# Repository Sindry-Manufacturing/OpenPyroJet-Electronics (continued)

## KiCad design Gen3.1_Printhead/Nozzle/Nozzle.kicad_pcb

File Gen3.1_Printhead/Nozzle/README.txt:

This directory contains KiCAD 5.1.x design files for a set of PCB's that make up the OpenPyroJet Gen 3.1 printhead. 
 
The directory could be better named as Printhead (as opposed to Nozzle), but I believe thats hard to do once a KiCAD project has been started?

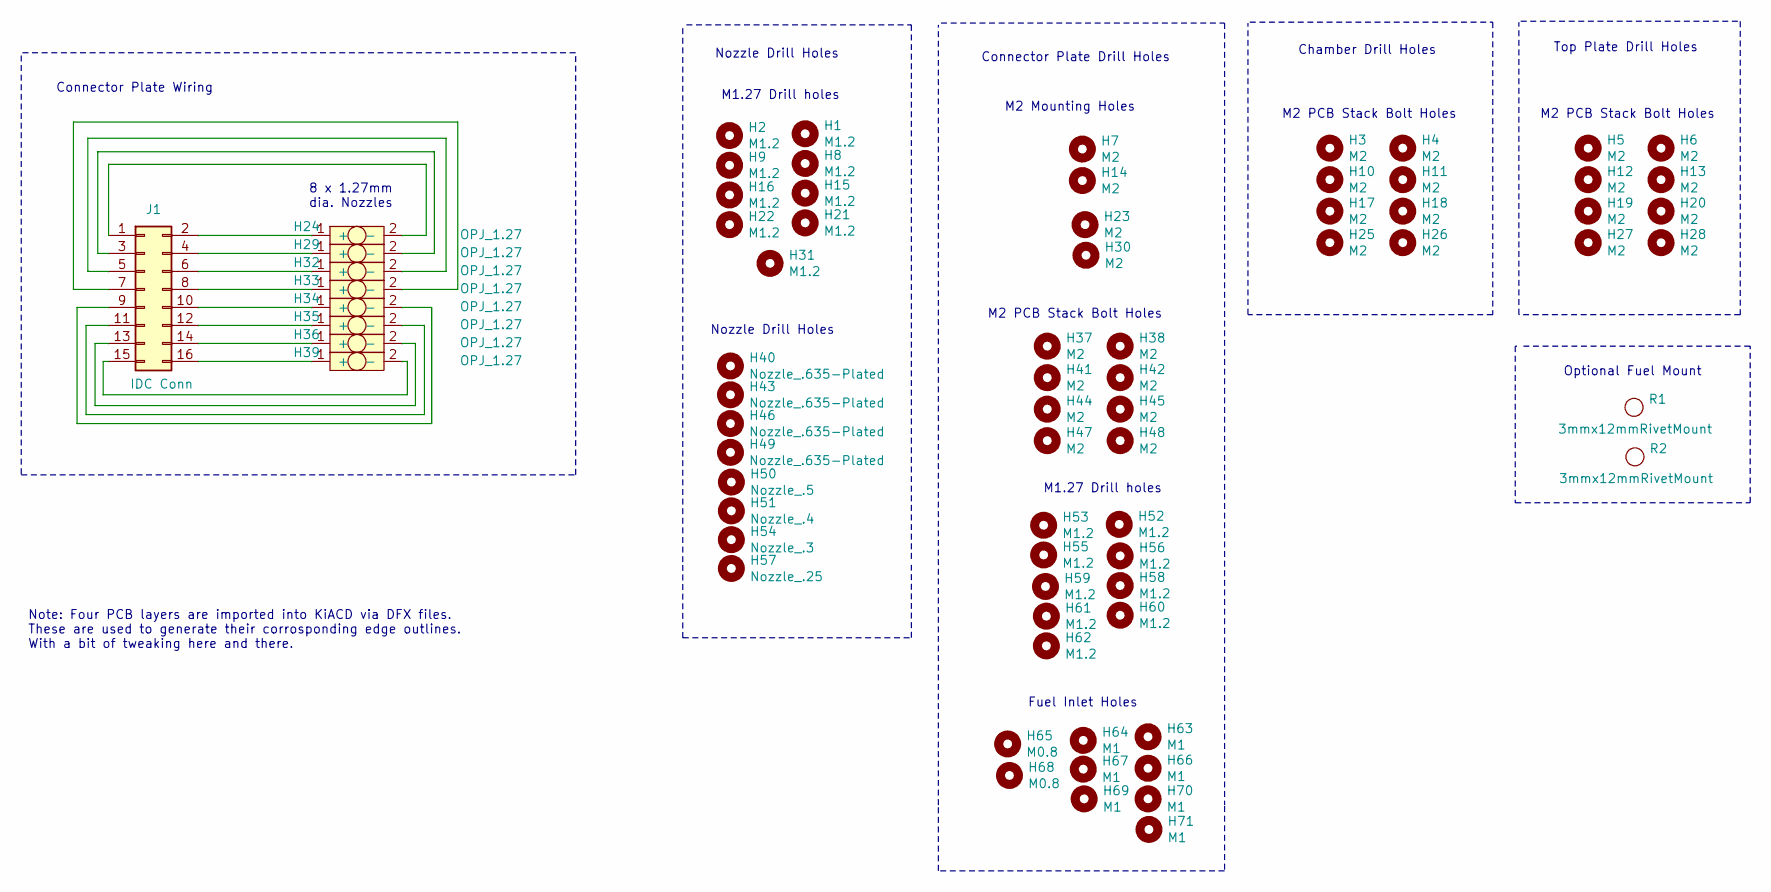
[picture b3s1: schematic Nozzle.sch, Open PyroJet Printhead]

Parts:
H1, H2, H8, H9, H15, H16, H21, H22, H31, H52, H53, H55, H56, H58, H59, H60, H61, H62: M1.2; MountingHole_1.2mm
H3, H4, H5, H6, H7, H10, H11, H12, H13, H14, H17, H18, H19, H20, H23, H25, H26, H27, H28, H30, H37, H38, H41, H42, H44, H45, H47, H48: M2; MountingHole_2.2mm_M2
H24, H29, H32, H33, H34, H35, H36, H39: OPJ_1.27
H40, H43, H46, H49: Nozzle_.635-Plated; Nozzle_0.635-Plated
H50: Nozzle_.5; Nozzle_0.5
H51: Nozzle_.4; Nozzle_0.4
H54: Nozzle_.3; Nozzle_0.3
H57: Nozzle_.25; Nozzle_0.25
H63, H64, H66, H67, H69, H70, H71: M1; MountingHole_1mm
H65, H68: M0.8; MountingHole_0.8mm
J1: IDC Conn; PinSocket_2x08_P2.54mm_Vertical
R1, R2: 3mmx12mmRivetMount; 3mmx12mmHollowRivet

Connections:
unnamed: H24.1 (+), J1.2
unnamed: H24.2 (-), J1.1
unnamed: H29.1 (+), J1.4
unnamed: H29.2 (-), J1.3
unnamed: H32.1 (+), J1.6
unnamed: H32.2 (-), J1.5
unnamed: H33.1 (+), J1.8
unnamed: H33.2 (-), J1.7
unnamed: H34.1 (+), J1.10
unnamed: H34.2 (-), J1.9
unnamed: H35.1 (+), J1.12
unnamed: H35.2 (-), J1.11
unnamed: H36.1 (+), J1.14
unnamed: H36.2 (-), J1.13
unnamed: H39.1 (+), J1.16
unnamed: H39.2 (-), J1.15

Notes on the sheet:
8 x 1.27mm dia. Nozzles
Optional Fuel Mount
M2 Mounting Holes
Connector Plate Wiring
Note: Four PCB layers are imported into KiACD via DFX files. These are used to generate their corrosponding edge outlines. With a bit of tweaking here and there.
M2 PCB Stack Bolt Holes
M1.27 Drill holes
Connector Plate Drill Holes
Nozzle Drill Holes
Chamber Drill Holes
Top Plate Drill Holes
Fuel Inlet Holes

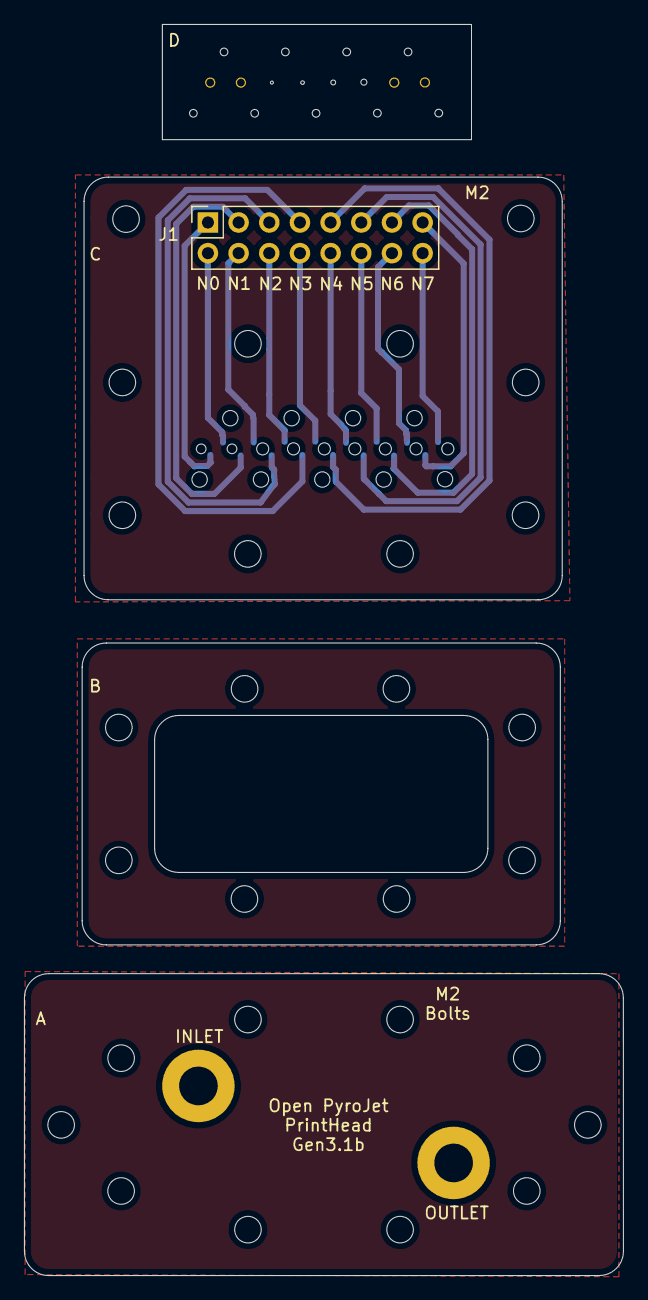
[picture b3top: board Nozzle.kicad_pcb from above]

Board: 2 copper layers, 49.6 x 103.6 mm, 74 parts (0 on the bottom side), 16 nets.

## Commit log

2022-03-18 initial import of Controller and Driver PCB KiCAD 5.1 designs
2022-03-22 final PCB KiCAD design files for V0.5 as sent off for manufacture at JLCPCB 2022-03-22
2022-03-27 Adding in the Gen3.1 printhead KiCAD PCB design files
2022-03-27 adding in Printhead schematic diagram
2022-03-29 adding in Gen3.1a Conector PCB inlet modifications - hole reduced from 1.27mm to 1mm, or 0.8mm
2022-03-29 updated Printhead to Gen3.1b - Nozzle screw holes swapped from 1.27mm to 0.635mm. Added labels to each board to help with identification
2022-04-03 Repo now has an updated panel with 3mm holes in top plate. Each layer is alphabet coded.
2022-04-26 Adding in PCB testing software
2022-04-26 adding in explination doc
2022-04-26 adding PCB stencil files and updated BOM listings that include LCSC part nnumbers
2022-05-11 Updating Controller and Driver boards to version 0.6
2022-05-11 adding in ESP32 DAC to ADC121 check/test
2022-05-11 adding in test result chart
2022-05-11 updated Controller Test code
2022-05-12 Updated BOM spreadsheets with LCSC partnumbers. Changed schematic and voltage divider values
2022-06-10 adding in test code of V0.6 PCB
2022-06-11 fixes for VSW voltage readings
2022-06-14 Adding in version 0.7 KiACD design files
2022-06-14 changes to make Rotary Encoder work better. Still configured for VSW monitoring
2023-02-08 added fusion archive files
    Added the complete base design files from fusion 360 and eaglePCB to allow editing and modification of the underlying design.
2023-07-11 Update README.md
    added license text.
2023-07-11 Add files via upload
    Added CERN OHL-S-V2
2023-07-11 Create LICENSE
    added a proper detectable license template for included software.
